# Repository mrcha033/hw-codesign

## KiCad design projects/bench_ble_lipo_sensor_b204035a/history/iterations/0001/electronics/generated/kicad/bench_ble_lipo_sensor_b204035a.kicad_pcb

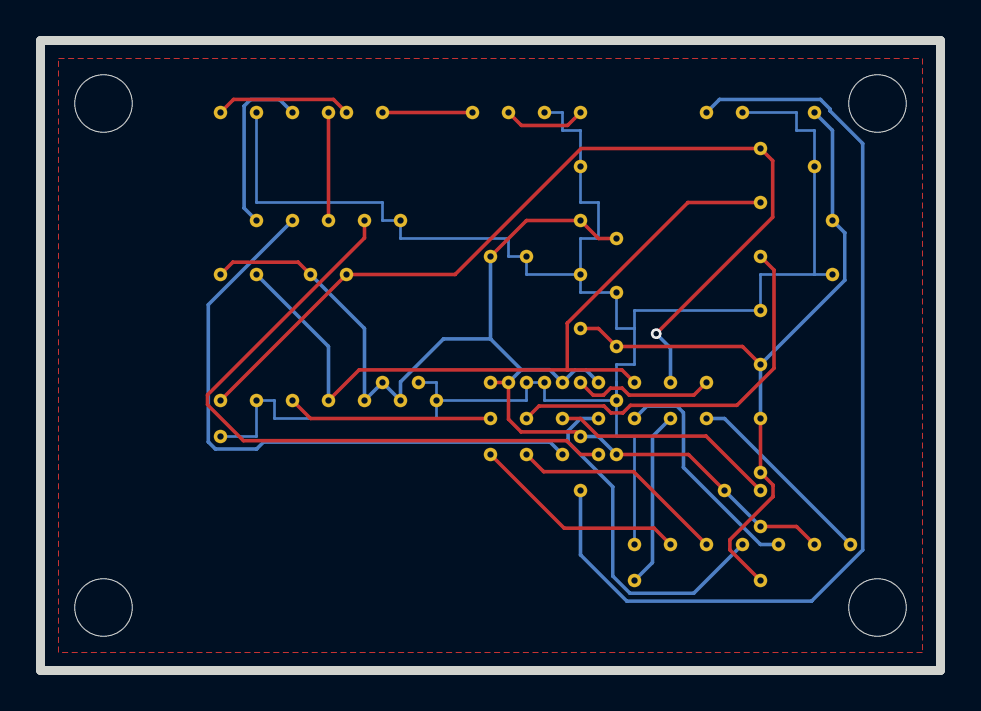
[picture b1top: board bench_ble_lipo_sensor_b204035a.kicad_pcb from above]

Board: 2 copper layers, 50.0 x 35.0 mm, 23 parts (0 on the bottom side), 23 nets.

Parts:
BT1: LiPo 400mAh; JST_PH_S2B-PH-K_1x02_P2.00mm_Horizontal
C1, C2: 100nF; C_0603_1608Metric
C3, C4: 10uF; C_1210_3225Metric
D1: USB ESD; SOT-23-6
F1: 500mA Fuse; MIDI_Fuse
H1, H2, H3, H4: MountingHole; MountingHole_3.2mm_Pad
J1: USB-C CHARGE; USB_C_GCT_USB4105
J2: SWD DEBUG; FTSH-105
LD1: 3V3 LDO; SOT-23-5
Q1: Ideal Diode; SOT-23-6
R1, R2: 4K7; R_0603_1608Metric
R3: 1K; R_0603_1608Metric
R4: 10K; R_0603_1608Metric
U1: nRF52840; nRF52840-QIAA
U2: LiPo Charger; SOT-23-8
U3: Fuel Gauge; VSON-9_2x3mm_P0.5mm
U5: Temp/Humidity; DFN-8-1EP_2x2.5mm_P0.5mm

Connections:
CHG_ISET: R4.1, U2.8
CHG_STAT: U1.7, U2.6
FUEL_ALRT: U1.9, U3.3
GND: BT1.2, C1.2, C2.2, C3.2, C4.2, D1.5, J1.2, J2.1, LD1.2, LD1.4, Q1.3, R4.2, U1.2, U2.2, U2.4, U3.4, U5.2, U5.7, U5.8
I2C_SCL: R1.2, U1.5, U3.2, U5.4
I2C_SDA: R2.2, U1.6, U3.1, U5.1
LED_BLE: R3.2, U1.10
NRST: J2.4, U1.11
SWDCLK: J2.7, U1.14
SWDIO: J2.2, U1.15
SWO: J2.3, U1.16
TEMP_INT: U1.8, U5.3
UART_RX: J2.8, U1.13
UART_TX: J2.5, U1.12
USB_DM: D1.4, U1.18
USB_DM_RAW: D1.3, J1.4
USB_DP: D1.2, U1.17
USB_DP_RAW: D1.1, J1.3
USB_FUSED: F1.2, Q1.1
USB_PROT: Q1.2, U2.1
USB_VBUS: F1.1, J1.1
V3V3: C1.1, C2.1, C4.1, J2.6, LD1.1, LD1.5, R1.1, R2.1, R3.1, U1.1, U1.3, U1.4, U2.3, U2.7, U3.8, U5.5, U5.6
VBAT: BT1.1, C3.1, LD1.3, U2.5, U3.5, U3.6, U3.7, U3.9

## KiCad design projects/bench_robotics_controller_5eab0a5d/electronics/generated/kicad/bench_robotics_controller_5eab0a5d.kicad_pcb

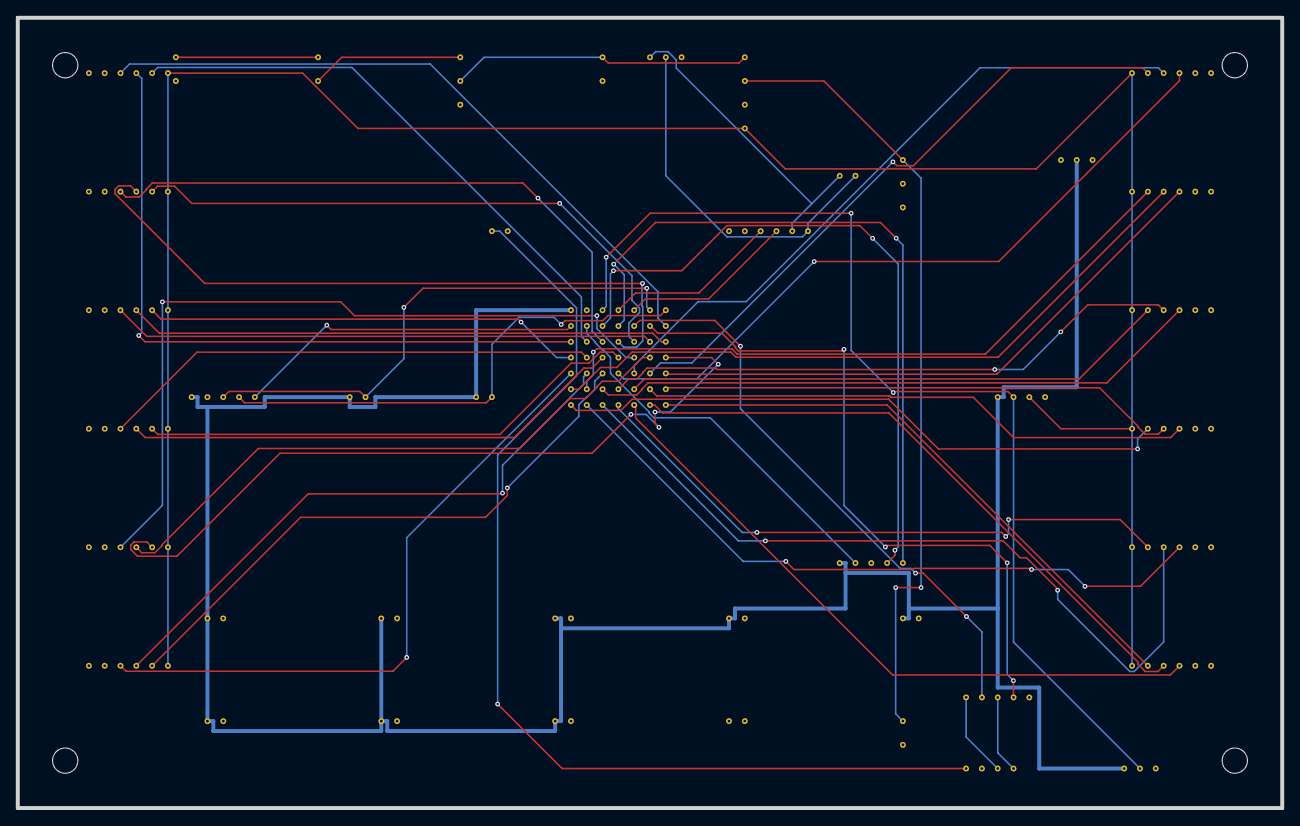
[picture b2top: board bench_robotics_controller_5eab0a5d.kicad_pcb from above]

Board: 4 copper layers, 160.0 x 100.0 mm, 46 parts (0 on the bottom side), 60 nets.

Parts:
C1, C2, C3, C4, C5, C6, C7, C8: 100nF; C_0603_1608Metric
C9: 22uF; C_1206_3216Metric
C10: 10uF 50V; C_1210_3225Metric
D1: 33V TVS; D_SMC
D2: USB ESD; SOT-23-6
F1: 80A SERVICE FUSE; MIDI_Fuse
H1, H2, H3, H4: MountingHole; MountingHole_3.2mm_Pad
J1: 24V INPUT; MicroFit_2Pin
J2: E-STOP; Phoenix_3Pin
J3: CAN; MicroFit_3Pin
J4: SWD; FTSH-105
J5: USB-C; USB_C_GCT_USB4105
J11: MOTOR_IO_1; MicroFit_8Pin
J12: MOTOR_IO_2; MicroFit_8Pin
J13: MOTOR_IO_3; MicroFit_8Pin
J14: MOTOR_IO_4; MicroFit_8Pin
J15: MOTOR_IO_5; MicroFit_8Pin
J16: MOTOR_IO_6; MicroFit_8Pin
J17: MOTOR_IO_7; MicroFit_8Pin
J18: MOTOR_IO_8; MicroFit_8Pin
J19: MOTOR_IO_9; MicroFit_8Pin
J20: MOTOR_IO_10; MicroFit_8Pin
J21: MOTOR_IO_11; MicroFit_8Pin
J22: MOTOR_IO_12; MicroFit_8Pin
Q1: IDEAL DIODE; SOT-23-6
Q2: E-STOP GATE; SOT-23-6
R1: 120R; R_0603_1608Metric
R2, R3: 4K7; R_0603_1608Metric
R4: 100K; R_0603_1608Metric
U1: STM32H743; LQFP-100_14x14mm_P0.5mm
U2: ICM-42688-P; LGA-14
U3: eFuse; VQFN-24-1EP
U4: 5V Buck; WQFN-30
U5: 3V3 Buck; VQFN-16
U6: CAN PHY; SOIC-8_3.9x4.9mm_P1.27mm

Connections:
CANH: J3.1, R1.1, U6.5
CANL: J3.2, R1.2, U6.6
CAN_RX: U1.4, U6.3
CAN_TX: U1.5, U6.4
ESTOP_GATE: J11.6, J12.6, J13.6, J14.6, J15.6, J16.6, J17.6, J18.6, J19.6, J20.6, J21.6, J22.6, Q2.3, U3.4
ESTOP_IN: J2.2, Q2.2, U1.3
GND: C1.2, C2.2, C3.2, C4.2, C5.2, C6.2, C7.2, C8.2, C9.2, C10.2, D1.2, D2.5, J1.2, J2.3, J3.3, J4.3, J5.2, J11.2, J12.2, J13.2, J14.2, J15.2, J16.2, J17.2, J18.2, J19.2, J20.2, J21.2, J22.2, Q1.3, Q2.4, R4.2, U1.2, U2.2, U3.3, U4.3, U5.3, U6.2
I2C_IMU_SCL: R2.2, U1.6, U2.3
I2C_IMU_SDA: R3.2, U1.7, U2.4
IMU_INT: U1.8, U2.5
MOTOR1_CURRENT: J11.4, U1.15
MOTOR1_ENC: J11.5, U1.16
MOTOR1_PWM: J11.3, U1.14
MOTOR2_CURRENT: J12.4, U1.18
MOTOR2_ENC: J12.5, U1.19
MOTOR2_PWM: J12.3, U1.17
MOTOR3_CURRENT: J13.4, U1.21
MOTOR3_ENC: J13.5, U1.22
MOTOR3_PWM: J13.3, U1.20
MOTOR4_CURRENT: J14.4, U1.24
MOTOR4_ENC: J14.5, U1.25
MOTOR4_PWM: J14.3, U1.23
MOTOR5_CURRENT: J15.4, U1.27
MOTOR5_ENC: J15.5, U1.28
MOTOR5_PWM: J15.3, U1.26
MOTOR6_CURRENT: J16.4, U1.30
MOTOR6_ENC: J16.5, U1.31
MOTOR6_PWM: J16.3, U1.29
MOTOR7_CURRENT: J17.4, U1.33
MOTOR7_ENC: J17.5, U1.34
MOTOR7_PWM: J17.3, U1.32
MOTOR8_CURRENT: J18.4, U1.36
MOTOR8_ENC: J18.5, U1.37
MOTOR8_PWM: J18.3, U1.35
MOTOR9_CURRENT: J19.4, U1.39
MOTOR9_ENC: J19.5, U1.40
MOTOR9_PWM: J19.3, U1.38
MOTOR10_CURRENT: J20.4, U1.42
MOTOR10_ENC: J20.5, U1.43
MOTOR10_PWM: J20.3, U1.41
MOTOR11_CURRENT: J21.4, U1.45
MOTOR11_ENC: J21.5, U1.46
MOTOR11_PWM: J21.3, U1.44
MOTOR12_CURRENT: J22.4, U1.48
MOTOR12_ENC: J22.5, U1.49
MOTOR12_PWM: J22.3, U1.47
NRST: J4.5, U1.11
SWCLK: J4.4, U1.10
SWDIO: J4.2, U1.9
USB_DM: D2.4, U1.13
USB_DM_RAW: D2.3, J5.4
USB_DP: D2.2, U1.12
USB_DP_RAW: D2.1, J5.3
USB_VBUS: J5.1, R4.1
V3V3: C1.1, C2.1, C3.1, C4.1, C5.1, C6.1, C7.1, C8.1, J2.1, J4.1, Q2.1, R2.1, R3.1, U1.1, U2.1, U5.2
V5: C9.1, J11.1, J12.1, J13.1, J14.1, J15.1, J16.1, J17.1, J18.1, J19.1, J20.1, J21.1, J22.1, U4.2, U5.1, U6.1
VBAT: D1.1, Q1.2, U3.1
VBAT_FUSED: F1.2, Q1.1
VBAT_RAW: F1.1, J1.1
VSYS: C10.1, U3.2, U4.1

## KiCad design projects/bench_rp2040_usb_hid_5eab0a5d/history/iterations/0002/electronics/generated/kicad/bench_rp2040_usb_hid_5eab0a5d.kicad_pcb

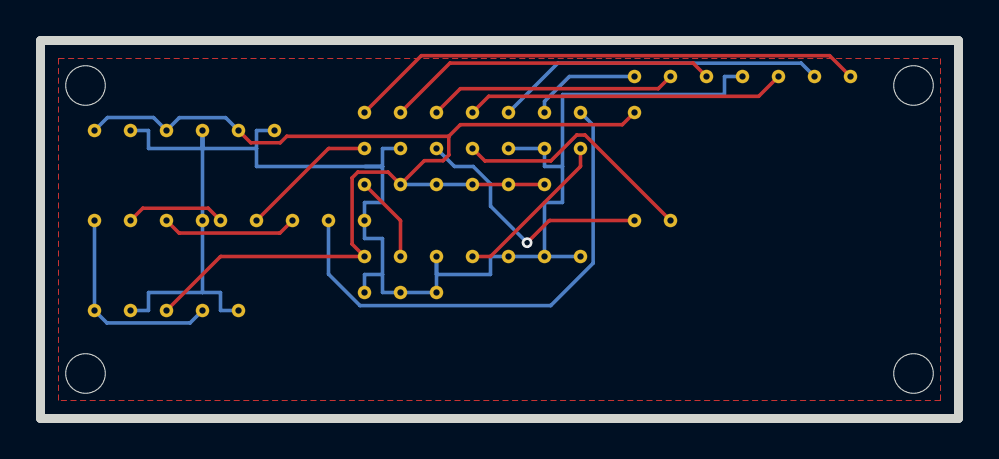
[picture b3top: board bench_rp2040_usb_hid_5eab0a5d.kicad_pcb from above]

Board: 2 copper layers, 51.0 x 21.0 mm, 15 parts (0 on the bottom side), 17 nets.

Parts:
C1, C2: 100nF; C_0402_1005Metric
C3: 10uF; C_0603_1608Metric
C4: 10uF USB_IN; C_0603_1608Metric
D1: USB ESD; SOT-23-6
H1, H2, H3, H4: MountingHole; MountingHole_2.2mm_Pad
J1: USB-C POWER; USB_C_GCT_USB4105
J2: SWD 10-pin; PinHeader_2x05_P2.54mm_Vertical
U1: 3V3 LDO; SOT-23-5
U2: RP2040; QFN-56-1EP_7x7mm_P0.4mm_EP3.2x3.2mm
U3: 2MB QSPI; SOIC-8_3.9x4.9mm_P1.27mm
X1: 12MHz XTAL; Crystal_SMD_HC-49S

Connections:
GND: C1.2, C2.2, C3.2, C4.2, D1.5, J1.4, J2.3, J2.5, J2.6, J2.7, J2.8, J2.9, J2.10, U1.2, U2.16, U2.33, U2.34, U3.4
QSPI_CLK: U2.5, U3.6
QSPI_CS: U2.6, U3.1
QSPI_D2: U2.2, U3.3
QSPI_D3: U2.1, U3.7
QSPI_MISO: U2.3, U3.2
QSPI_MOSI: U2.4, U3.5
SWCLK: J2.4, U2.40
SWDIO: J2.2, U2.41
USB_DM: D1.4, U2.11
USB_DM_RAW: D1.3, J1.3
USB_DP: D1.2, U2.12
USB_DP_RAW: D1.1, J1.2
USB_VBUS: C4.1, J1.1, U1.1
V3V3: C1.1, C2.1, C3.1, J2.1, U1.3, U2.44, U2.45, U2.46, U2.47, U2.48, U3.8
XIN: U2.17, X1.1
XOUT: U2.18, X1.2

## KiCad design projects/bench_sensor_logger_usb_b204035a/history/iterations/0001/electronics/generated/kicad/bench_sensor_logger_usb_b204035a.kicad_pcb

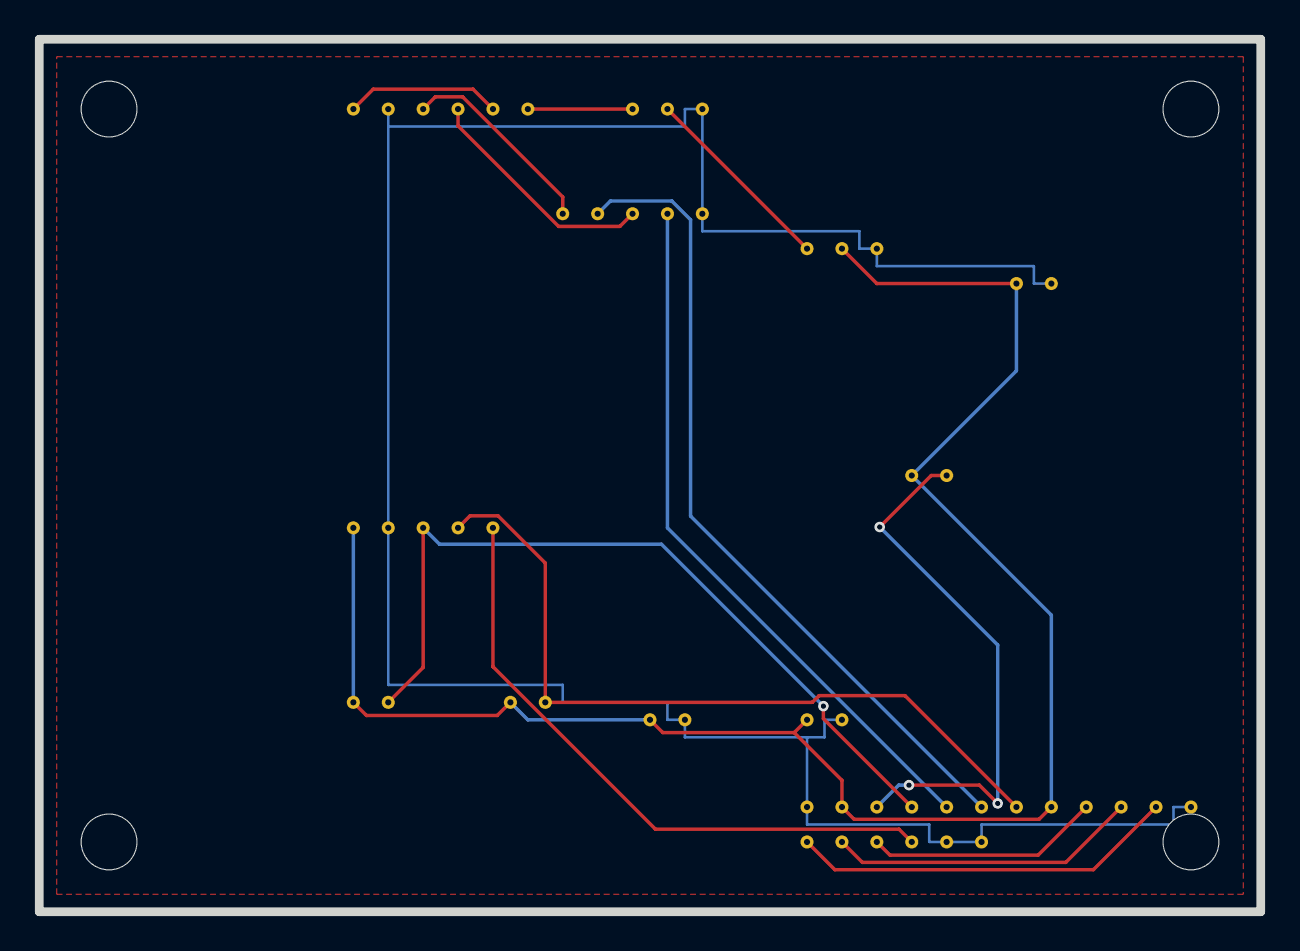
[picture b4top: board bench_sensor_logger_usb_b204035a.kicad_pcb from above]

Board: 2 copper layers, 70.0 x 50.0 mm, 18 parts (0 on the bottom side), 16 nets.

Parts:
C1, C2: 100nF; C_0603_1608Metric
C9: 22uF; C_1206_3216Metric
D1: USB ESD; SOT-23-6
F1: 500mA Fuse; MIDI_Fuse
H1, H2, H3, H4: MountingHole; MountingHole_3.2mm_Pad
J1: USB-C POWER; USB_C_GCT_USB4105
J2: UART DEBUG; FTSH-105
Q1: Ideal Diode; SOT-23-6
R1, R2, R3: 4K7; R_0603_1608Metric
U1: ESP32-S3-WROOM-1
U2: ICM-42688-P; LGA-14
U3: 3V3 Buck; VQFN-16

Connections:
BOOT: J2.4, U1.27
ESP_EN: R3.2, U1.3
GND: C1.2, C2.2, C9.2, D1.5, J1.2, J2.5, Q1.3, U1.1, U1.40, U1.41, U2.2, U3.3
I2C_IMU_SCL: R1.2, U1.12, U2.3
I2C_IMU_SDA: R2.2, U1.15, U2.4
IMU_INT: U1.39, U2.5
UART_RX: J2.3, U1.36
UART_TX: J2.2, U1.37
USB_DM: D1.4, U1.13
USB_DM_RAW: D1.3, J1.4
USB_DP: D1.2, U1.14
USB_DP_RAW: D1.1, J1.3
USB_FUSED: F1.2, Q1.1
USB_PROT: Q1.2, U3.1
USB_VBUS: F1.1, J1.1
V3V3: C1.1, C2.1, C9.1, J2.1, R1.1, R2.1, R3.1, U1.2, U2.1, U3.2
